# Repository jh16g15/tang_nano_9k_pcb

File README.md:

# tang_nano_9k_pcb
Sipeed Tang Nano 9K  Carrier board design (WIP)

This board is designed to add extra interfaces to the Tang Nano 9K, such as:

- SPI Ethernet (W5500)
- Trackball
- PS/2 Keyboard
- Audio (I2S DAC)

Mini-DIN6 footprint (PS/2) provided by
https://github.com/4x1md/kicad_libraries/tree/master/Custom_Footprints.pretty

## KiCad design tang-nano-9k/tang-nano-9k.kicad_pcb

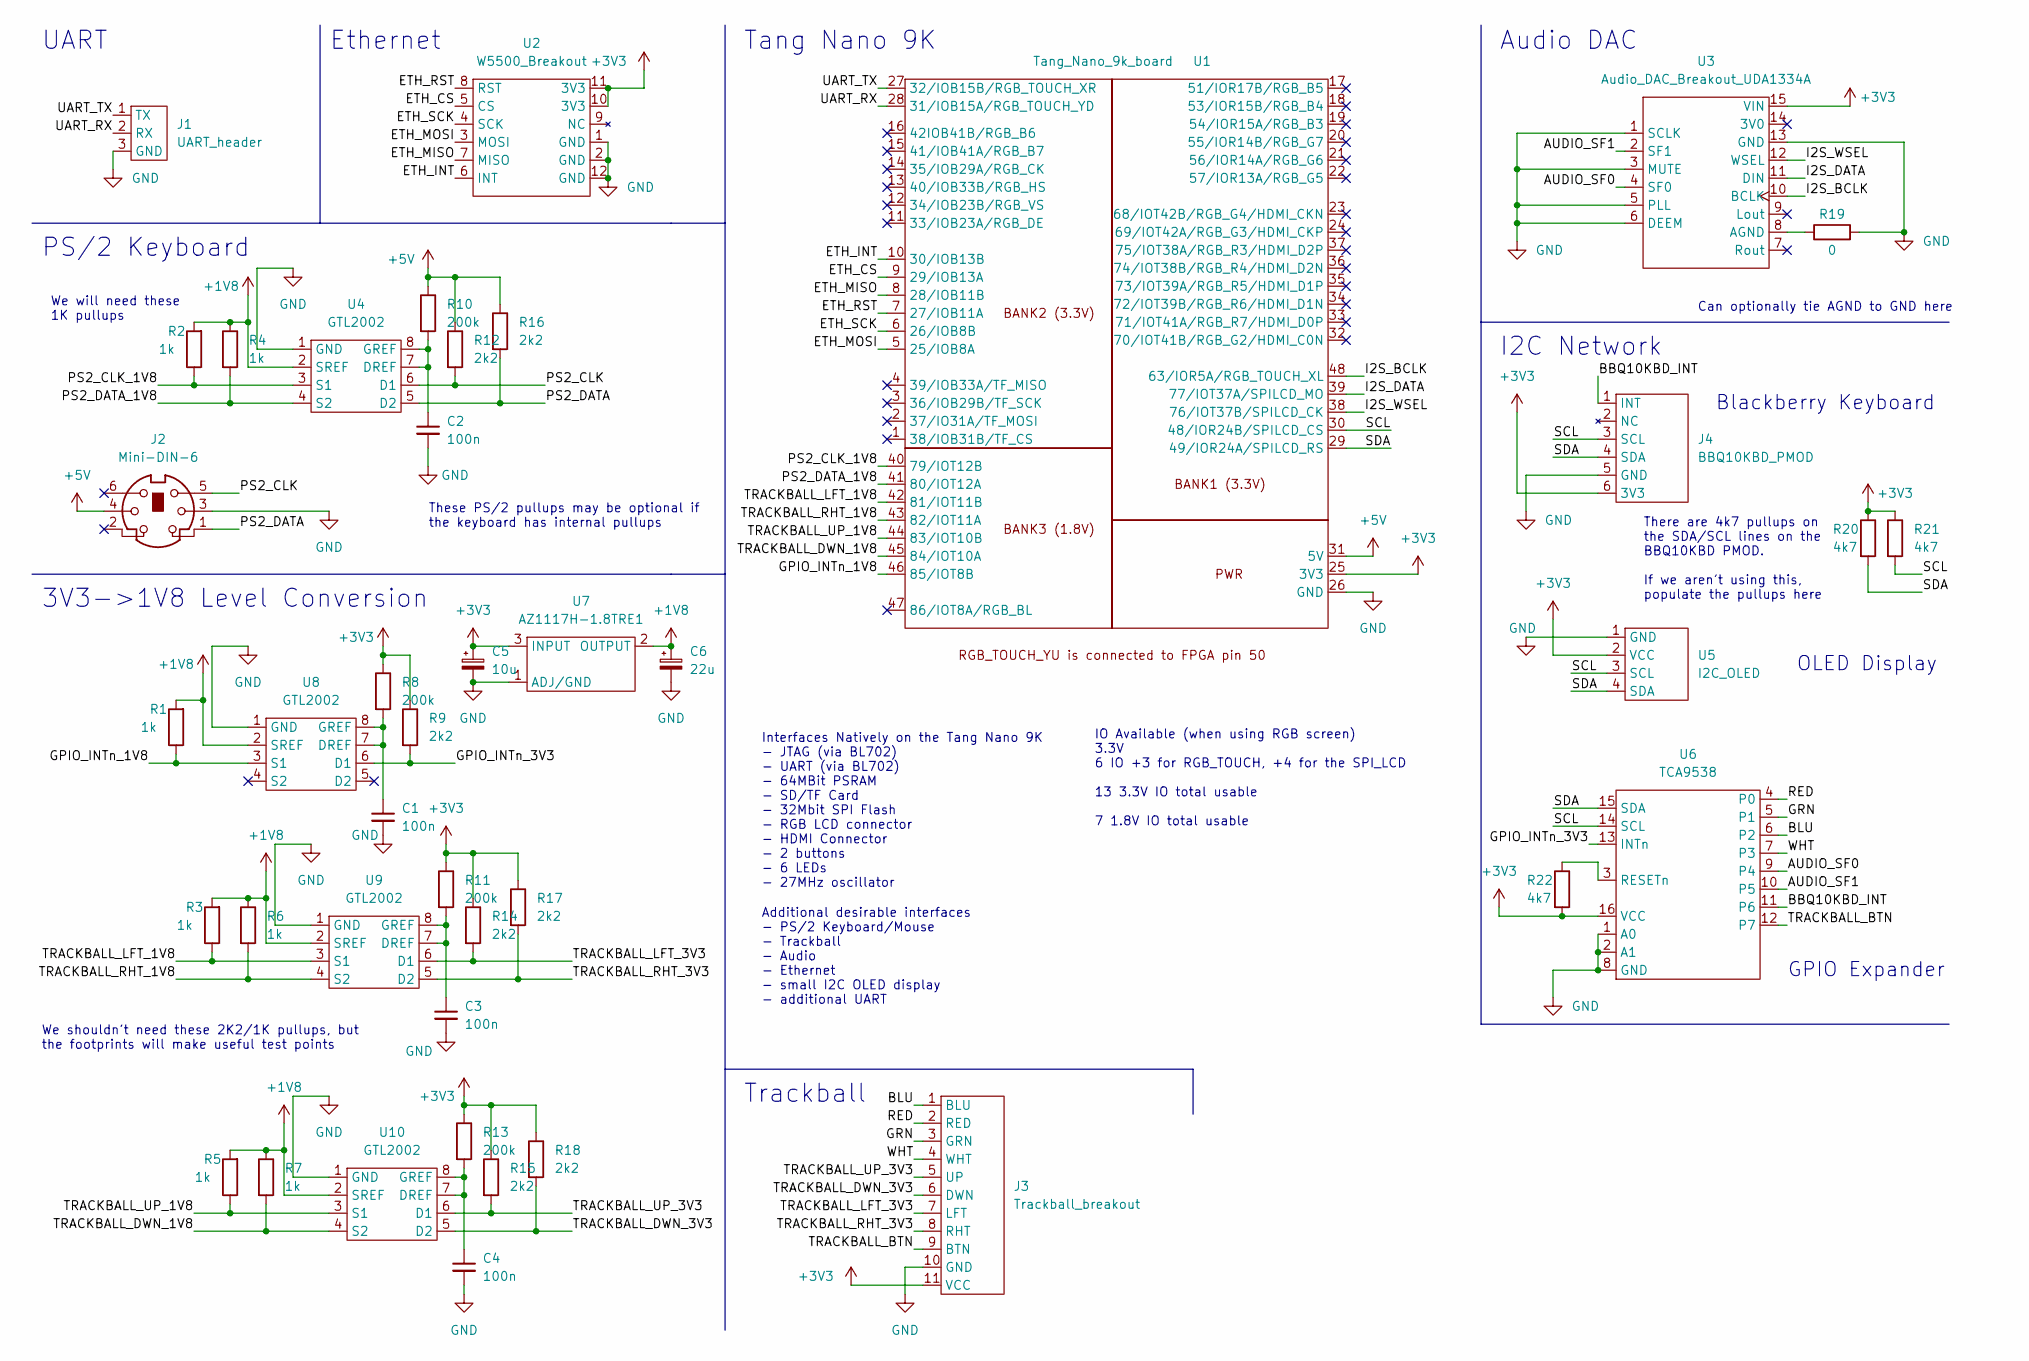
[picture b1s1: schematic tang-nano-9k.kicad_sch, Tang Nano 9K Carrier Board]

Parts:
C1, C2, C3, C4: 100n; C_Disc_D3.8mm_W2.6mm_P2.50mm
C5: 10u; CP_Radial_D5.0mm_P2.00mm
C6: 22u; CP_Radial_D5.0mm_P2.00mm
J1: UART_header; PinHeader_1x03_P2.54mm_Vertical
J2: Mini-DIN-6; Connector_Mini-DIN_Female_6Pin_2rows
J3: Trackball_breakout
J4: BBQ10KBD_PMOD; PinHeader_1x06_P2.54mm_Horizontal
R1, R2, R3, R4, R5, R6, R7: 1k; R_Axial_DIN0207_L6.3mm_D2.5mm_P10.16mm_Horizontal
R8, R10, R11, R13: 200k; R_Axial_DIN0207_L6.3mm_D2.5mm_P10.16mm_Horizontal
R9, R12, R14, R15, R16, R17, R18: 2k2; R_Axial_DIN0207_L6.3mm_D2.5mm_P10.16mm_Horizontal
R19: 0; R_Axial_DIN0204_L3.6mm_D1.6mm_P5.08mm_Horizontal
R20, R21, R22: 4k7; R_Axial_DIN0207_L6.3mm_D2.5mm_P10.16mm_Horizontal
U1: Tang_Nano_9k_board; Tang Nano 9K
U2: W5500_Breakout
U3: Audio_DAC_Breakout_UDA1334A; UDA1334_Breakout
U4, U8, U9, U10: GTL2002; TSSOP-8_3x3mm_P0.65mm
U5: I2C_OLED; i2c_oled_128x64
U6: TCA9538; SSOP-16_5.3x6.2mm_P0.65mm
U7: AZ1117H-1.8TRE1; SOT-223-3_TabPin2

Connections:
+1V8: C6.1, R1.2, R2.2, R3.2, R4.1, R5.2, R6.1, R7.1, U4.2 (SREF), U7.2 (OUTPUT), U8.2 (SREF), U9.2 (SREF), U10.2 (SREF)
+3V3: C5.1, J3.11 (VCC), J4.6 (3V3), R8.1, R9.1, R11.1, R13.1, R14.1, R15.1, R17.1, R18.1, R20.1, R21.1, R22.2, U1.25 (3V3), U2.10 (3V3), U2.11 (3V3), U3.15 (VIN), U5.2 (VCC), U6.16 (VCC), U7.3 (INPUT)
+5V: J2.4, R10.1, R12.1, R16.1, U1.31 (5V)
/AUDIO_SF0: U3.4 (SF0), U6.9 (P4)
/AUDIO_SF1: U3.2 (SF1), U6.10 (P5)
/BBQ10KBD_INT: J4.1 (INT), U6.11 (P6)
/BLU: J3.1 (BLU), U6.6 (P2)
/ETH_CS: U1.9 (29/IOB13A), U2.5 (CS)
/ETH_INT: U1.10 (30/IOB13B), U2.6 (INT)
/ETH_MISO: U1.8 (28/IOB11B), U2.7 (MISO)
/ETH_MOSI: U1.5 (25/IOB8A), U2.3 (MOSI)
/ETH_RST: U1.7 (27/IOB11A), U2.8 (RST)
/ETH_SCK: U1.6 (26/IOB8B), U2.4 (SCK)
/GPIO_INTn_1V8: R1.1, U1.46 (85/IOT8B), U8.3 (S1)
/GPIO_INTn_3V3: R9.2, U6.13 (INTn), U8.6 (D1)
/GRN: J3.3 (GRN), U6.5 (P1)
/I2S_BCLK: U1.48 (63/IOR5A/RGB_TOUCH_XL), U3.10 (BCLK)
/I2S_DATA: U1.39 (77/IOT37A/SPILCD_MO), U3.11 (DIN)
/I2S_WSEL: U1.38 (76/IOT37B/SPILCD_CK), U3.12 (WSEL)
/PS2_CLK: J2.5, R12.2, U4.6 (D1)
/PS2_CLK_1V8: R2.1, U1.40 (79/IOT12B), U4.3 (S1)
/PS2_DATA: J2.1, R16.2, U4.5 (D2)
/PS2_DATA_1V8: R4.2, U1.41 (80/IOT12A), U4.4 (S2)
/RED: J3.2 (RED), U6.4 (P0)
/SCL: J4.3 (SCL), R21.2, U1.30 (48/IOR24B/SPILCD_CS), U5.3 (SCL), U6.14 (SCL)
/SDA: J4.4 (SDA), R20.2, U1.29 (49/IOR24A/SPILCD_RS), U5.4 (SDA), U6.15 (SDA)
/TRACKBALL_BTN: J3.9 (BTN), U6.12 (P7)
/TRACKBALL_DWN_1V8: R7.2, U1.45 (84/IOT10A), U10.4 (S2)
/TRACKBALL_DWN_3V3: J3.6 (DWN), R18.2, U10.5 (D2)
/TRACKBALL_LFT_1V8: R3.1, U1.42 (81/IOT11B), U9.3 (S1)
/TRACKBALL_LFT_3V3: J3.7 (LFT), R14.2, U9.6 (D1)
/TRACKBALL_RHT_1V8: R6.2, U1.43 (82/IOT11A), U9.4 (S2)
/TRACKBALL_RHT_3V3: J3.8 (RHT), R17.2, U9.5 (D2)
/TRACKBALL_UP_1V8: R5.1, U1.44 (83/IOT10B), U10.3 (S1)
/TRACKBALL_UP_3V3: J3.5 (UP), R15.2, U10.6 (D1)
/UART_RX: J1.2 (RX), U1.28 (31/IOB15A/RGB_TOUCH_YD)
/UART_TX: J1.1 (TX), U1.27 (32/IOB15B/RGB_TOUCH_XR)
/WHT: J3.4 (WHT), U6.7 (P3)
GND: C1.2, C2.2, C3.2, C4.2, C5.2, C6.2, J1.3 (GND), J2.3, J3.10 (GND), J4.5 (GND), R19.2, U1.26 (GND), U2.1 (GND), U2.2 (GND), U2.12 (GND), U3.1 (SCLK), U3.3 (MUTE), U3.5 (PLL), U3.6 (DEEM), U3.13 (GND), U4.1 (GND), U5.1 (GND), U6.1 (A0), U6.2 (A1), U6.8 (GND), U7.1 (ADJ/GND), U8.1 (GND), U9.1 (GND), U10.1 (GND)
unnamed: C1.1, R8.2, U8.7 (DREF), U8.8 (GREF)
unnamed: C2.1, R10.2, U4.7 (DREF), U4.8 (GREF)
unnamed: C3.1, R11.2, U9.7 (DREF), U9.8 (GREF)
unnamed: C4.1, R13.2, U10.7 (DREF), U10.8 (GREF)
unnamed: R19.1, U3.8 (AGND)
unnamed: R22.1, U6.3 (RESETn)

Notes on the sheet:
We will need these 1K pullups
There are 4k7 pullups on the SDA/SCL lines on the BBQ10KBD PMOD. If we aren't using this, populate the pullups here
Audio DAC
IO Available (when using RGB screen) 3.3V 6 IO +3 for RGB_TOUCH, +4 for the SPI_LCD 13 3.3V IO total usable 7 1.8V IO total usable
Tang Nano 9K
We shouldn't need these 2K2/1K pullups, but the footprints will make useful test points
These PS/2 pullups may be optional if the keyboard has internal pullups
PS/2 Keyboard
Additional desirable interfaces - PS/2 Keyboard/Mouse - Trackball - Audio - Ethernet - small I2C OLED display - additional UART
Ethernet
Interfaces Natively on the Tang Nano 9K - JTAG (via BL702) - UART (via BL702) - 64MBit PSRAM - SD/TF Card - 32Mbit SPI Flash - RGB LCD connector - HDMI Connector - 2 buttons - 6 LEDs - 27MHz oscillator
GPIO Expander
Can optionally tie AGND to GND here
Trackball
UART
I2C Network
OLED Display
3V3->1V8 Level Conversion
Blackberry Keyboard

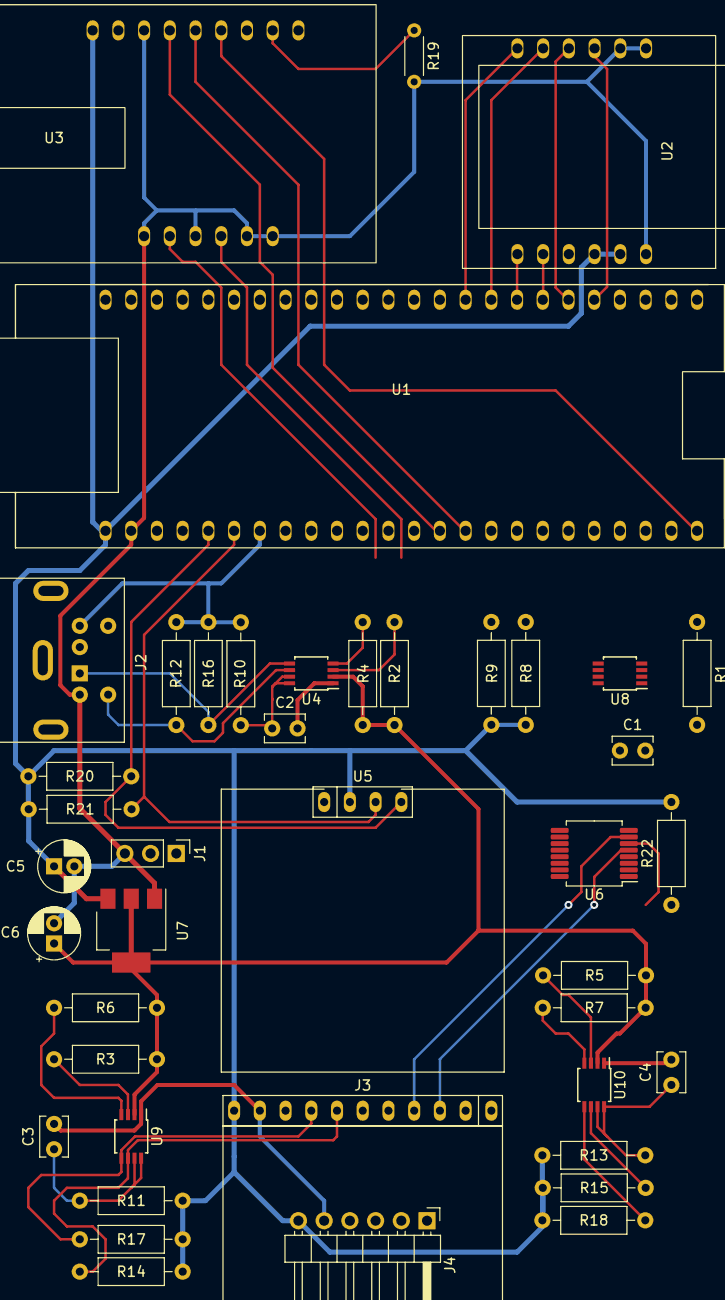
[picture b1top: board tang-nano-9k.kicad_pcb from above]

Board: 2 copper layers, 42 parts (0 on the bottom side), 45 nets.

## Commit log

2022-06-05 Updated schematic
2022-06-05 fixed UDA1334 connections and added NC to unused pins across the schematic
2022-06-06 updated schematic with footprints
2022-06-08 Added pullups to GPIO expander INTn pin Initial placement and partial routing
